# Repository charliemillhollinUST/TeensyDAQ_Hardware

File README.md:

The schematic and PCB were created in KiCad.

Contact <mill70882@stthomas.edu> for access to the TeensyDAQ repository.

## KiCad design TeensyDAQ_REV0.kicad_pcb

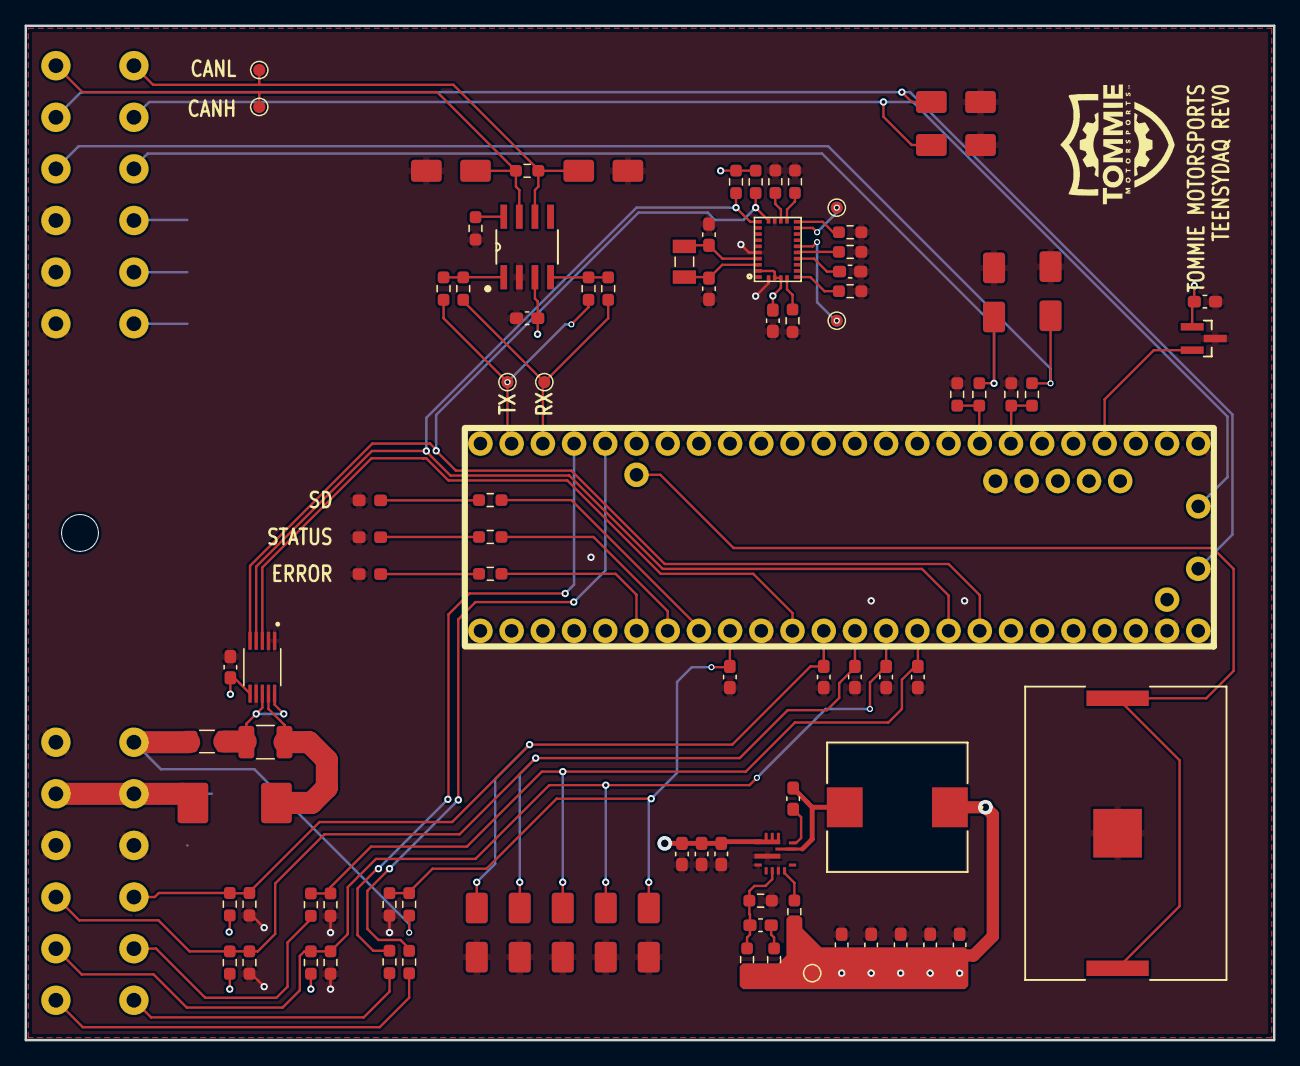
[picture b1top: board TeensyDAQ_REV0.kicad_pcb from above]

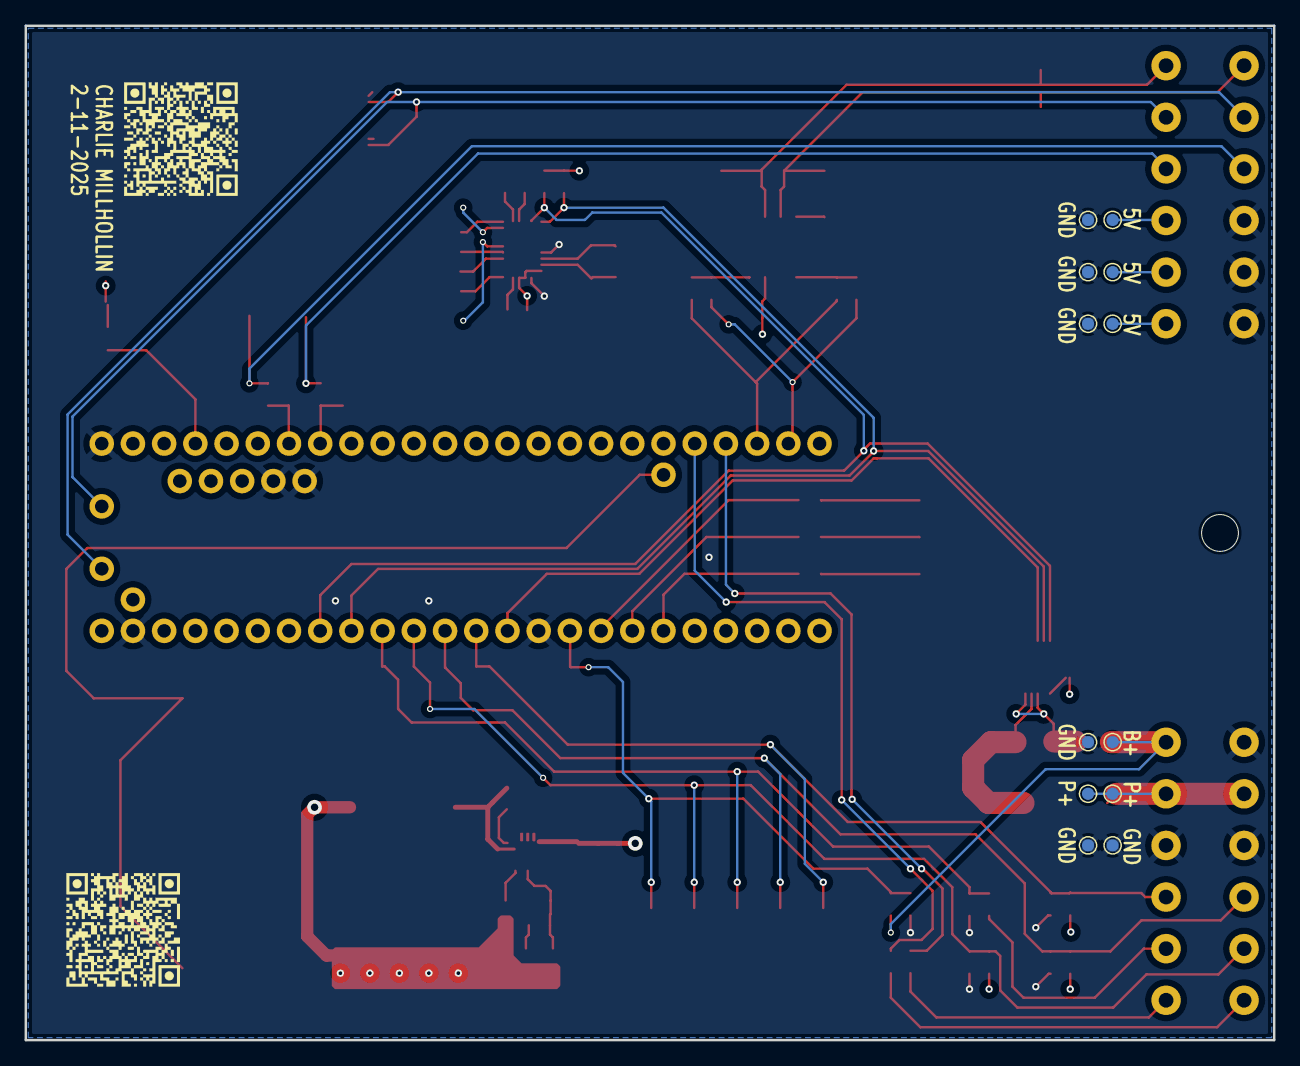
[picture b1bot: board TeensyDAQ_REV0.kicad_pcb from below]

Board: 4 copper layers, 101.6 x 82.6 mm, 105 parts (12 on the bottom side), 57 nets.

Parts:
5V, 5V103, 5V#2, 5V#3: TestPoint; TestPoint_Pad_D1.0mm
B100: 3034; 3034_KEY
B+: TestPoint; TestPoint_Pad_D1.0mm
C100, C101, C105, C106, C107, C108, C109: 10u; C_0603_1608Metric_Pad1.08x0.95mm_HandSolder
C102, C116, C117: 100n; C_0603_1608Metric_Pad1.08x0.95mm_HandSolder
C103, C110, C111, C112, C113, C114, C115, C120, C121: 0.1u; C_0603_1608Metric_Pad1.08x0.95mm_HandSolder
C104: 100p; C_0603_1608Metric_Pad1.08x0.95mm_HandSolder
C118, C119: 22p; C_0603_1608Metric_Pad1.08x0.95mm_HandSolder
CANH: TestPoint; TestPoint_Pad_D1.0mm
CANL: TestPoint; TestPoint_Pad_D1.0mm
D100, D101, D102: LED; LED_0603_1608Metric_Pad1.05x0.95mm_HandSolder
D103: B340; D_SMC
D104, D105, D106, D107, D108, D109, D110, D111, D112, D113, D115: SMAJ5.0A; D_SMA
F100: Fuse; Fuse_1206_3216Metric
GND: TestPoint; TestPoint_Pad_D1.0mm
GND#2, GND#3, GND#4, GND#5, GND#6: TestPoint; TestPoint_Pad_D1.0mm
J100: ATM13-12PA-12PB-BM01
L100: 3.3u; IND_IHLP-4040DZ_VIS
P+: TestPoint; TestPoint_Pad_D1.0mm
P+#2: TestPoint; TestPoint_Pad_D1.0mm
Q100: Teensy4_1
R100, R101, R102: 10; R_0603_1608Metric_Pad0.98x0.95mm_HandSolder
R103, R119, R121: 100k; R_0603_1608Metric_Pad0.98x0.95mm_HandSolder
R104: 20k; R_0603_1608Metric_Pad0.98x0.95mm_HandSolder
R105: 73.2k; R_0603_1608Metric_Pad0.98x0.95mm_HandSolder
R106, R113, R115, R117, R128, R129, R133, R134, R135: 10k; R_0603_1608Metric_Pad0.98x0.95mm_HandSolder
R107, R108, R109, R110, R111, R130, R131, R132, R140, R141: 0; R_0603_1608Metric_Pad0.98x0.95mm_HandSolder
R112: 120; R_0603_1608Metric_Pad0.98x0.95mm_HandSolder
R114, R116: 15k; R_0603_1608Metric_Pad0.98x0.95mm_HandSolder
R118: 3k; R_0603_1608Metric_Pad0.98x0.95mm_HandSolder
R120, R122, R123, R124, R125, R126: DNP; R_0603_1608Metric_Pad0.98x0.95mm_HandSolder
R127: 0.1; R_1210_3225Metric_Pad1.30x2.65mm_HandSolder
RX: TestPoint; TestPoint_Pad_D1.0mm
TP100, TP101: TestPoint; TestPoint_Pad_D1.0mm
TX: TestPoint; TestPoint_Pad_D1.0mm
U100: TPS56637RPAR; RPA0010A
U101: INA226AIDGSR
U102: BNO055; LGA28R50P4X10_380X520X100
U103: SN65HVD230DR; D8
U104: DRV5032FBDBZR; DBZ0003A-IPC_A
Y100: ABS07-32.768KHZ-T; XTAL_ABS07-32.768KHZ-T

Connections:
+3V3: C114.1, C116.2, C120.1, C121.1, Q100.-2 (3.3V), Q100.-5 (3.3V), R119.2, R121.2, R125.2, R128.2, R129.2, U101.6 (VS), U102.3 (VDD), U102.4 (NBOOT_LOAD_PIN), U102.28 (VDDIO), U103.3 (VCC), U104.1 (VCC)
+5V: 5V.1, 5V103.1, 5V#2.1, 5V#3.1, C105.2, C106.2, C107.2, C108.2, C109.2, J100.10 (Pin_10_1), J100.11 (Pin_11_1), J100.12 (Pin_12_1), L100.1, Q100.-3 (Vin), R103.2, R104.2, R105.2
/Analog/Battery_IN+: B+.1, F100.1, J100.13 (Pin_1_2), R117.2
/Analog/CVT_Thermistor+: C111.1, D110.1 (A1), J100.21 (Pin_9_2), Q100.15, R121.1, R122.2
/Analog/Engine_Thermistor+: C110.1, D113.1 (A1), J100.16 (Pin_4_2), Q100.14, R119.1, R120.2
/Analog/Hall_Signal1: D109.1 (A1), J100.4 (Pin_4_1), R113.2
/Analog/Hall_Signal1_u: Q100.5, R113.1, R114.2
/Analog/Hall_Signal2: D104.1 (A1), J100.9 (Pin_9_1), R115.2
/Analog/Hall_Signal2_u: Q100.6, R115.1, R116.2
/Analog/Magnet_u: Q100.2, U104.2 (OUT)
/Analog/Thermistor3_u: C113.1, D111.1 (A1), J100.20 (Pin_8_2), Q100.16, R125.1, R126.2
/Analog/VDIV1+: J100.17 (Pin_5_2), R123.2
/Analog/VDIV1_u: C112.1, D112.1 (A1), Q100.17, R123.1, R124.2
/Analog/VMeas_BATu: C115.1, D115.1 (A1), Q100.41, R117.1, R118.2
/CAN/CANH: CANH.1, D107.1 (A1), J100.6 (Pin_6_1), R112.2, U103.7 (CANH)
/CAN/CANL: CANL.1, D106.1 (A1), J100.7 (Pin_7_1), R112.1, U103.6 (CANL)
/CAN/CAN_RXu: Q100.30, R107.2, R108.2, RX.1
/CAN/CAN_TXu: Q100.31, R109.2, R110.2, TX.1
/Enclosure Connectors/P1: J100.18 (Pin_6_2), R141.1
/Enclosure Connectors/P2: J100.19 (Pin_7_2), R140.1
/Enclosure Connectors/Power_OUT+: C100.2, C101.2, C102.2, D103.1 (K), J100.14 (Pin_2_2), J100.23 (Pin_11_2), P+.1, P+#2.1, U100.8 (VIN)
/Enclosure Connectors/USB_D+: D105.1 (A1), J100.8 (Pin_8_1), Q100.-9 (D+_Device)
/Enclosure Connectors/USB_D-: D108.1 (A1), J100.5 (Pin_5_1), Q100.-8 (D-_Device)
/Gyro/I2C_SCL: Q100.19, R129.1, U101.5 (SCL), U102.19 (COM1)
/Gyro/I2C_SDA: Q100.18, R128.1, U101.4 (SDA), U102.20 (COM0)
/Power Biasing/INA226A_ALERT: Q100.13, U101.3 (ALERT)
CUR_S_+: F100.2, R127.1, U101.8 (VBUS), U101.10 (IN+)
CUR_S_-: D103.2 (A), R127.2, U101.9 (IN-)
ERROR_LED: Q100.38, R102.1
GND: B100.3, C100.1, C101.1, C102.1, C105.1, C106.1, C107.1, C108.1, C109.1, C110.2, C111.2, C112.2, C113.2, C114.2, C115.2, C116.1, C117.2, C118.2, C119.1, C120.2, C121.2, D100.1 (K), D101.1 (K), D102.1 (K), D104.2 (A2), D105.2 (A2), D106.2 (A2), D107.2 (A2), D108.2 (A2), D109.2 (A2), D110.2 (A2), D111.2 (A2), D112.2 (A2), D113.2 (A2), D115.2 (A2), GND.1, GND#2.1, GND#3.1, GND#4.1, GND#5.1, GND#6.1, J100.1 (Pin_1_1), J100.2 (Pin_2_1), J100.3 (Pin_3_1), J100.15 (Pin_3_2), J100.22 (Pin_10_2), J100.24 (Pin_12_2), Q100.-1 (GND), Q100.-4 (GND), Q100.-6 (GND), Q100.-13 (GND), Q100.-14 (GND), R106.1, R111.2, R114.1, R116.1, R118.1, R120.1, R122.1, R124.1, R126.1, R130.2, R131.2, R132.2, R133.2, R134.2, R135.2, U100.3 (AGND), U100.9 (PGND), U100.10 (MODE), U101.1 (A1), U101.2 (A0), U101.7 (GND), U102.2 (GND), U102.18 (COM2), U102.25 (GNDIO), U103.2 (GND), U104.3 (GND)
unnamed: C104.2, R104.1
unnamed: D100.2 (A), R102.2
unnamed: D101.2 (A), R101.2
unnamed: D102.2 (A), R100.2
unnamed: Q100.28, R140.2
unnamed: Q100.29, R141.2
unnamed: C103.2, U100.7 (BOOT)
unnamed: C104.1, R105.1, R106.2, U100.2 (FB)
unnamed: R103.1, U100.4 (PG)
unnamed: C103.1, L100.2, U100.6 (SW)
unnamed: C117.1, U102.9 (CAP)
unnamed: R133.1, U102.17 (COM3)
unnamed: TP101.1, U102.14 (INT)
unnamed: TP100.1, U102.11 (NRESET)
unnamed: R130.1, U102.10 (PIN10)
unnamed: R131.1, U102.15 (PIN15)
unnamed: R132.1, U102.16 (PIN16)
unnamed: R134.1, U102.6 (PS0)
unnamed: R135.1, U102.5 (PS1)
unnamed: R107.1, R109.1, U103.1 (D)
unnamed: R108.1, R110.1, U103.4 (R)
unnamed: R111.1, U103.8 (RS)
RTC_BAT+: B100.1, B100.2, Q100.-19 (VBAT)
SD_LED: Q100.40, R101.1
XIN32: C118.1, U102.27 (XIN32), Y100.1
XOUT32: C119.2, U102.26 (XOUT32), Y100.2
uLED: Q100.39, R100.1

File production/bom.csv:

Designator,Footprint,Quantity,Value,LCSC Part #
"5V_3, 5V_2, 5V, 5V103, B+, CANH, CANL, GND_6, GND_5, GND_4, GND_3, GND_2, GND, P+_2, P+, RX, TP100, TP101, TX",TestPoint_Pad_D1.0mm,19,TestPoint,
B100,3034_KEY,1,3034,
"C100, C101, C105, C106, C107, C108, C109",0603,7,10u,
"C102, C116, C117",0603,3,100n,
"C103, C110, C111, C112, C113, C114, C115, C120, C121",0603,9,0.1u,
C104,0603,1,100p,
"C118, C119",0603,2,22p,
"D100, D101, D102",0603,3,LED,
D103,D_SMC,1,B340,
"D104, D105, D106, D107, D108, D109, D110, D111, D112, D113, D115",D_SMA,11,SMAJ5.0A,
F100,1206,1,Fuse,
J100,ATM13-12PA-12PB-BM01,1,~,
L100,IND_IHLP-4040DZ_VIS,1,3.3u,
Q100,Teensy4_1,1,~,
"R100, R101, R102",0603,3,10,
"R103, R119, R121",0603,3,100k,
R104,0603,1,20k,
R105,0603,1,73.2k,
"R106, R113, R115, R117, R128, R129, R133, R134, R135",0603,9,10k,
"R107, R108, R109, R110, R111, R130, R131, R132, R140, R141",0603,10,0,
R112,0603,1,120,
"R114, R116",0603,2,15k,
R118,0603,1,3k,
"R120, R122, R123, R124, R125, R126",0603,6,DNP,
R127,1210,1,0.1,
U100,RPA0010A,1,TPS56637RPAR,
U101,INA226AIDGSR,1,INA226AIDGSR,
U102,LGA28R50P4X10_380X520X100,1,BNO055,
U103,D8,1,SN65HVD230DR,
U104,DBZ0003A-IPC_A,1,DRV5032FBDBZR,
Y100,XTAL_ABS07-32.768KHZ-T,1,ABS07-32.768KHZ-T,

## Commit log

2025-01-23 added gitignore
2025-01-23 Remove tracked files and update gitignore
2025-01-23 cleaned up routing on main page of schematic
2025-01-25 test commit
2025-02-11 Added gyro, current sense, removed servo control, added temp sense
2025-02-11 finished up schematic, added magnetic sensor, cleaned up pins, etc.
2025-02-11 cleaned up refdes
2025-02-11 final route. Needs revision and check of via placement.
2025-02-11 added ground planes and 4 layer. Ran DRC and checked out
2025-02-11 ran fabrication output to get basic quote. Need to run iBOM and add digikey links
2025-02-11 added more power tracks to power layer. re-ran fabrication output
2025-02-11 removed a VDIV input and changed it to a thermistor input. Re-ran fabrication output
2025-02-11 added 5V test point at caps
2025-02-11 added GND vias to copper pour next to i2c lines to hopefully reduce noise
2025-02-11 changed date lol
2025-02-12 added TVS diodes to external pins for protection. Ran fabrication output. Ran iBOM generation. All part links can be seen in the iBOM. Download and open to see this
2025-02-12 file cleanup
2025-02-12 initial release
2025-02-12 updated QR code to match github repository on silkscreen
2025-02-12 added images
2025-02-12 added power planes to correct layer. Added 10A 1206 fuse to battery input before current measurement resistor and reverse polarity diode
2025-02-12 updated QR code
2025-02-12 updated silkscreen
2025-02-12 updated power traces. Updated silkscreen
2025-02-14 commit for sanity
2025-02-14 larger silkscreen
2025-02-14 corrected template directory. From FDC103-01
2025-02-14 working through adding LED indicator silkscreen. Had to leave because Luke sprayed oil everywhere
2025-02-15 updated silkscreen. Re-ran fab toolkit and iBOM. Looking to order today
2025-02-15 added gnd via to clean up copper pour
